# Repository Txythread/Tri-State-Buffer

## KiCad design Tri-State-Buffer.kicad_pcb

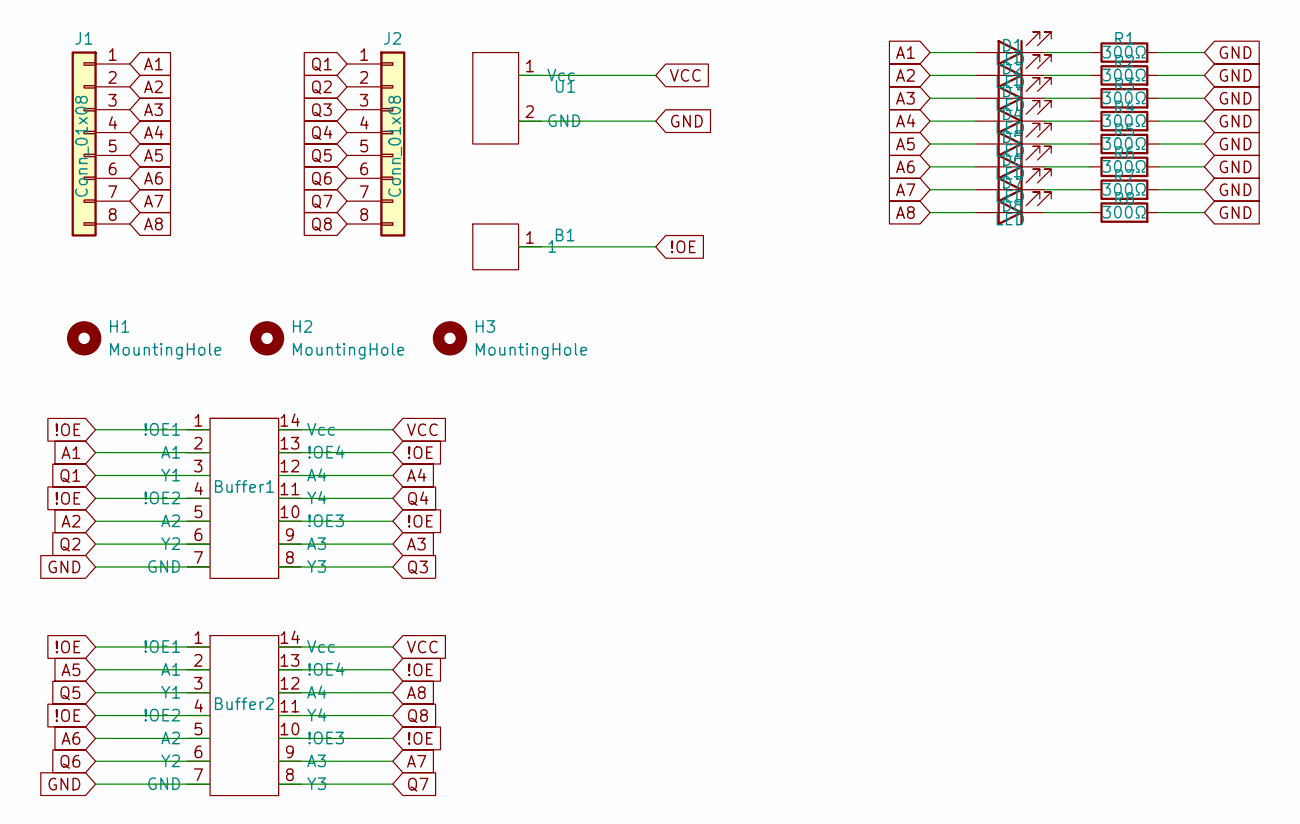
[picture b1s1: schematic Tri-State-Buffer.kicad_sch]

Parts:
B1: Single Bit Bus
Buffer1, Buffer2: SNx4HCT125
D1, D2, D3, D4, D5, D6, D7, D8: LED; LED_0805_2012Metric_Pad1.15x1.40mm_HandSolder
H1, H2, H3: MountingHole; MountingHole_2.1mm
J1, J2: Conn_01x08; PinHeader_1x08_P2.54mm_Vertical
R1, R2, R3, R4, R5, R6, R7, R8: 300Ω; R_0805_2012Metric_Pad1.20x1.40mm_HandSolder
U1: Vcc & GND

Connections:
!OE: B1.1, Buffer1.1 (!OE1), Buffer1.4 (!OE2), Buffer1.10 (!OE3), Buffer1.13 (!OE4), Buffer2.1 (!OE1), Buffer2.4 (!OE2), Buffer2.10 (!OE3), Buffer2.13 (!OE4)
A1: Buffer1.2 (A1), D1.2 (A), J1.1
A2: Buffer1.5 (A2), D2.2 (A), J1.2
A3: Buffer1.9 (A3), D3.2 (A), J1.3
A4: Buffer1.12 (A4), D4.2 (A), J1.4
A5: Buffer2.2 (A1), D5.2 (A), J1.5
A6: Buffer2.5 (A2), D6.2 (A), J1.6
A7: Buffer2.9 (A3), D7.2 (A), J1.7
A8: Buffer2.12 (A4), D8.2 (A), J1.8
GND: Buffer1.7 (GND), Buffer2.7 (GND), R1.2, R2.2, R3.2, R4.2, R5.2, R6.2, R7.2, R8.2, U1.2 (GND)
unnamed: D1.1 (K), R1.1
unnamed: D2.1 (K), R2.1
unnamed: D3.1 (K), R3.1
unnamed: D4.1 (K), R4.1
unnamed: D5.1 (K), R5.1
unnamed: D6.1 (K), R6.1
unnamed: D7.1 (K), R7.1
unnamed: D8.1 (K), R8.1
Q1: Buffer1.3 (Y1), J2.1
Q2: Buffer1.6 (Y2), J2.2
Q3: Buffer1.8 (Y3), J2.3
Q4: Buffer1.11 (Y4), J2.4
Q5: Buffer2.3 (Y1), J2.5
Q6: Buffer2.6 (Y2), J2.6
Q7: Buffer2.8 (Y3), J2.7
Q8: Buffer2.11 (Y4), J2.8
VCC: Buffer1.14 (Vcc), Buffer2.14 (Vcc), U1.1 (Vcc)

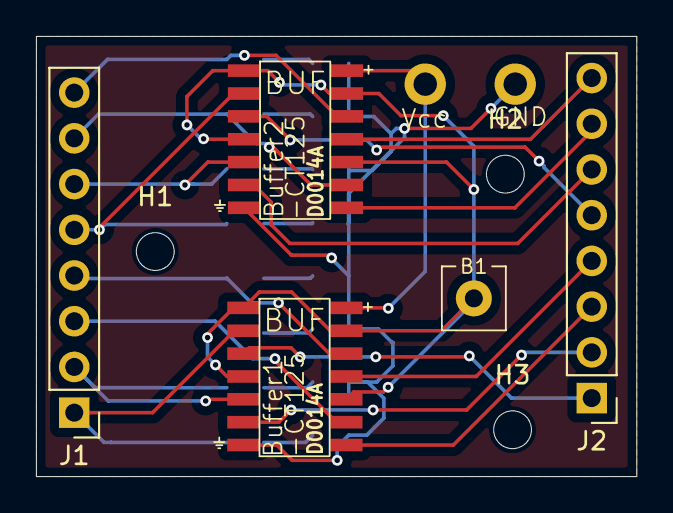
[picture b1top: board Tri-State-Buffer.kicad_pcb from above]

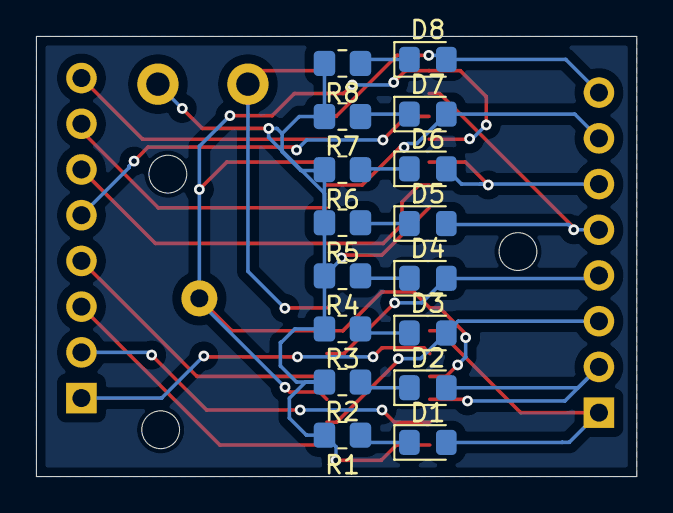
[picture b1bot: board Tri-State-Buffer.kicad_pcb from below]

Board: 2 copper layers, 33.4 x 24.5 mm, 25 parts (16 on the bottom side), 27 nets.

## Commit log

2025-08-22 Added Mounting Holes
2025-08-22 Create LICENSE
